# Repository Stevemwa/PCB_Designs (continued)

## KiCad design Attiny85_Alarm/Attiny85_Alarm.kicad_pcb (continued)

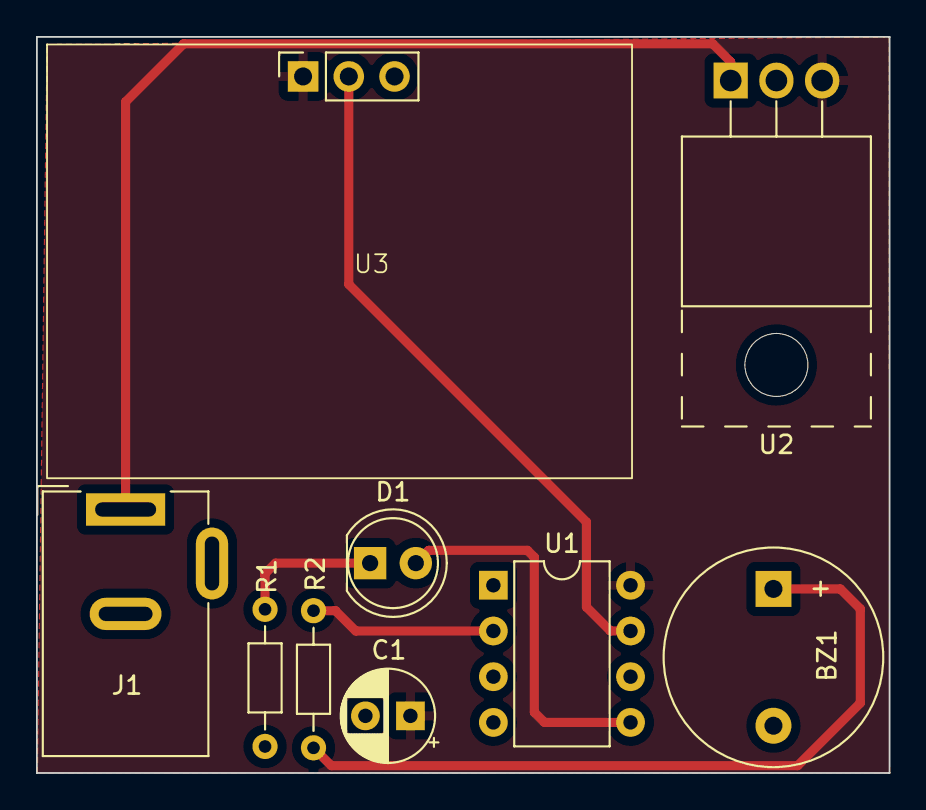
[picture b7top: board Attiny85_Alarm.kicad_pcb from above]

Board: 2 copper layers, 47.4 x 40.9 mm, 9 parts (0 on the bottom side), 8 nets.
